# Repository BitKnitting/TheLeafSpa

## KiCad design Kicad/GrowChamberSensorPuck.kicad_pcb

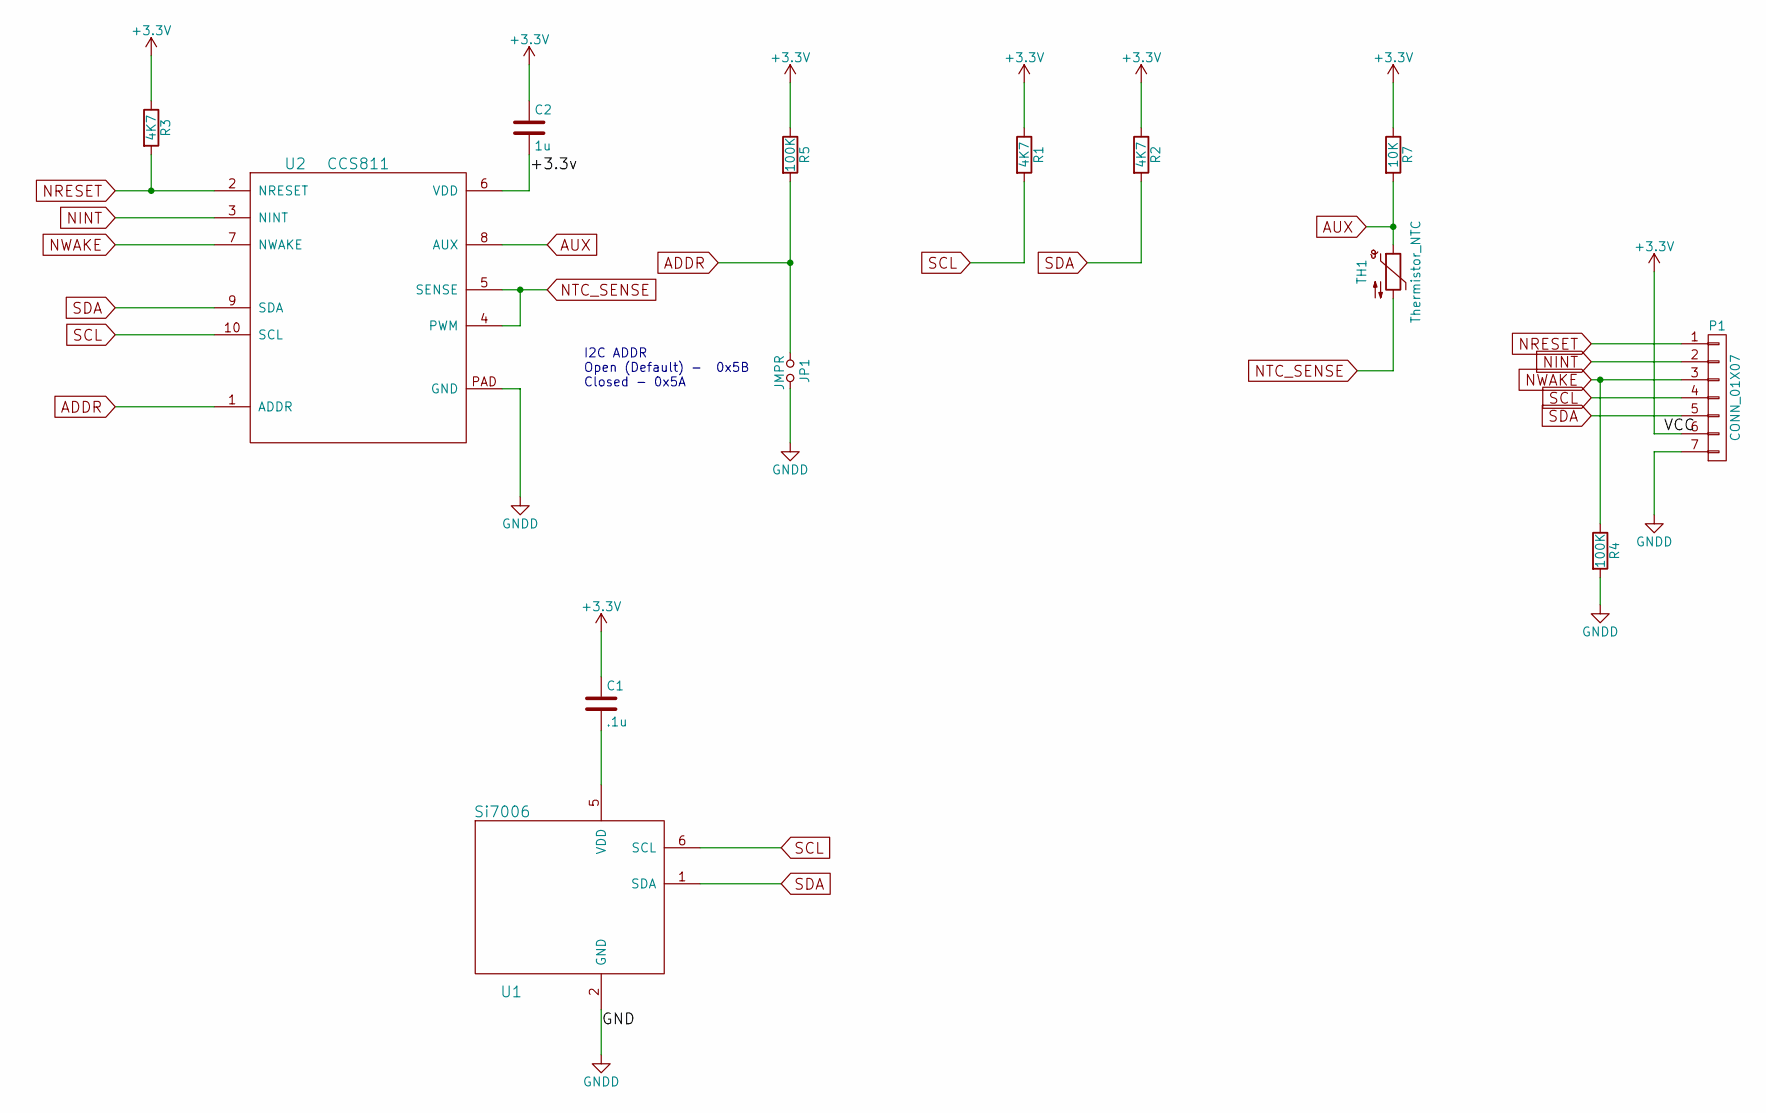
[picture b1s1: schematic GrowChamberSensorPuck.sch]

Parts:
C1: .1u; C_0805_HandSoldering
C2: 1u; C_0805_HandSoldering
JP1: JMPR; Socket_Strip_Straight_1x02_Pitch2.54mm
P1: CONN_01X07; Socket_Strip_Straight_1x07_Pitch2.54mm
R1, R2, R3: 4K7; C_0805_HandSoldering
R4, R5: 100K; C_0805_HandSoldering
R7: 10K; C_0805_HandSoldering
TH1: Thermistor_NTC; Socket_Strip_Straight_1x02_Pitch2.54mm
U1: Si7006
U2: CCS811

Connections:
+3V3: C1.1, C2.1, P1.6, R1.1, R2.1, R3.1, R5.1, R7.1
/+3.3v: C2.2, U2.6 (VDD)
ADDR: JP1.1, R5.2, U2.1 (ADDR)
AUX: R7.2, TH1.1, U2.8 (AUX)
GNDD: JP1.2, P1.7, R4.2, U1.2 (GND), U2.PAD (GND)
NINT: P1.2, U2.3 (NINT)
NRESET: P1.1, R3.2, U2.2 (NRESET)
NTC_SENSE: TH1.2, U2.4 (PWM), U2.5 (SENSE)
NWAKE: P1.3, R4.1, U2.7 (NWAKE)
unnamed: C1.2, U1.5 (VDD)
SCL: P1.4, R1.2, U1.6 (SCL), U2.10 (SCL)
SDA: P1.5, R2.2, U1.1 (SDA), U2.9 (SDA)

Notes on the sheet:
I2C ADDR Open (Default) - 0x5B Closed - 0x5A

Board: 2 copper layers, 13 parts (0 on the bottom side), 12 nets, no tracks yet.

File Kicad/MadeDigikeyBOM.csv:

Reference,Value,Quantity,Manf Part #,Digikey Part #,1,10,100,1000,Qty Avail,Link
"R4,R5",100K,2,ERJ-6GEYJ104V,P100KACT-ND,0.1,0.025,0.01,0.00451,523146,http://www.digikey.com/scripts/DkSearch/dksus.dll?WT.z_heade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
U1,Si7006,1,SI7006-A20-IM,336-3124-ND,2.08,2.08,1.7372,1.56551,2158,http://www.digikey.com/scripts/DkSearch/dksus.dll?WT.z_heade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
R7,10K,1,C0805JR-0710KL,311-10KARCT-ND,0.1,0.016,0.0066,0.00297,2775278,http://www.digikey.com/scripts/DkSearch/dksus.dll?WT.z_heade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
C2,1u,1,TMK212BJ105KG-T,587-1291-1-ND,0.16,0.115,0.0541,0.03139,231010,http://www.digikey.com/scripts/DkSearch/dksus.dll?WT.z_heade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
C1,.1u,1,CL21F104ZBCNNNC,1276-1007-1-ND,0.1,0.029,0.0128,0.00718,1016710,http://www.digikey.com/scripts/DkSearch/dksus.dll?WT.z_heade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
U2,CCS811,1,CCS811CT-ND,CCS811CT-ND,12.76,10.073,7.1632,7.1632,,http://www.digikey.com/scripts/DkSearch/dksus.dll?WT.z_heade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
"R1,R2,R3",4K7,3,RC0805FR-074K7L,311-4.70KCRCT-ND,0.1,0.019,0.0077,0.00345,2362052,http://www.digikey.com/scripts/DkSearch/dksus.dll?WT.z_heade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

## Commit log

2017-01-15 updates from January 14
2017-01-18 update for January 17
2017-01-18 January 18
2017-01-23 updated RelayTest.ino
2017-01-23 added turning pump on/off to RelayTest.ino
2017-01-24 updated RelayTest.ino to pump 2 minutes every hour instead of every half hour
2017-01-24 added CO2ReadAndLogTest.ino
2017-01-25 added CO2 test Arduino sketches
2017-01-26 updated Arduino CO2 test
2017-01-26 added Simple4ChannelRelayTest.ino
2017-02-01 running AdjustCO2Test.ino
2017-02-02 added SimpleRelayTest.ino
2017-02-02 updated simpleRelayTest.ino
2017-02-07 updated TheLeafSpa.ino
2017-02-09 added RTC time test
2017-02-10 added TurnLightsOnOffTest.ino
2017-02-11 start of Kicad
2017-02-12 added Kicad eeSchema for sensor puck
2017-02-15 updated Card detection as it relates to file open/close
2017-02-15 added footprints to sensor puck
2017-02-16 Feb 15 update
2017-02-16 added JellyBeanPartNumbersV2.csv
2017-02-16 added logging events like pump,LED on and off
2017-02-23 evolved Grow Sensor Puck schematic
2017-02-24 updated GrowChamberSensorPuck Kicad stuff
2017-03-01 updated TheLeafSpa.ino after first tests
2017-03-01 cleaned up files
2017-03-01 sent to OSHPark
2017-03-03 updated TheLeafSpa.ino to handle #define DEBUG correctly
2017-03-03 Added corrections to TheLeafSpa.ino after first run results
2017-03-03 Evolved CO2 valve open
2017-03-04 updated adjustCO2 in theLeafSpa.ino
2017-03-09 added Avg Temp, Humidity, and CO2 python project
2017-03-12 added MHZ19Test.ino
2017-03-16 added pwmTest1.py
2017-03-22 added sketches to test the flow meter
2017-03-22 added Flow Meter to TheLeafSpa.ino
2017-03-24 added images and datasheet for ph/ec-983 tear down
2017-03-29 updated theLeafSpa.ino with new memory management routines. Also updated python script that reads the logfile
2017-03-30 updated theLeafSpa.ino to remove memory leak because of excessive calls to opening a File and added AmtSRAM record
2017-03-30 changed pump on/off to be 1/2 hour instead of 15 minutes
2017-03-31 fixed a buffer overflow when adding stuff to the additionalInfo char array
2017-04-01 updated python script that reads the data logfile to create averages
2017-04-01 updated python script to create summary data from log file
2017-04-03 updated leafspa.py
2017-04-10 added si7006 and evolved python logfile script
2017-04-17 simple update
2017-05-13 added pinch valve Arduino code
